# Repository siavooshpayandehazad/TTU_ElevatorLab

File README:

=================================================================
#   ____  ____  _  _                                            #     
#  (_  _)(_  _)/ )( \                                           #
#    )(    )(  ) \/ (                                           #
#   (__)  (__) \____/                                           #
#   ____  ____  _  _   __  ____  ____                           #
#  (  _ \(  __)( \/ ) /  \(_  _)(  __)                          #
#   )   / ) _) / \/ \(  O ) )(   ) _)                           #
#  (__\_)(____)\_)(_/ \__/ (__) (____)                          #
#   ____  __    ____  _  _   __  ____  __  ____                 #
#  (  __)(  )  (  __)/ )( \ / _\(_  _)/  \(  _ \                #
#   ) _) / (_/\ ) _) \ \/ //    \ )( (  O ))   /                #
#  (____)\____/(____) \__/ \_/\_/(__) \__/(__\_)                #
#   __     __   ____   __  ____   __  ____  __  ____  _  _      #
#  (  )   / _\ (  _ \ /  \(  _ \ / _\(_  _)/  \(  _ \( \/ )     #
#  / (_/\/    \ ) _ ((  O ))   //    \ )( (  O ))   / )  /      #
#  \____/\_/\_/(____/ \__/(__\_)\_/\_/(__) \__/(__\_)(__/       #
=================================================================
CONTRIBUTORS: 				SUPERVISOR:	
	SIAVOOSH PAYANDEH AZAD			PEETER ELLERVEEE
        HANNES KINKS
        MUHAMMAD ADEEL TAJAMMUL
	MAREK GRENCSTEIN
	RALF ANARI
INSITUTE:       TALLINN UNIVERSITY OF TECHNOLOGY 
                COMPUTER ENGINEERING DEPARTMENT        
YEAR:           2014
---------------------------
WIKI:           http://ati.ttu.ee/wiki/index.php/LIFT
DEMO:           https://www.youtube.com/watch?v=4VPq74wMY-0
---------------------------
NOTE: 		THE UPDATES IN SUB-PROJECTS ARE AVAILABLE IN BRANCHES. WE WILL 
		MERGE FOR EACH RELEASE.

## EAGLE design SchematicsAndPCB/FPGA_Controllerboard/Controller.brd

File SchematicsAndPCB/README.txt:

AUTHOR: SIAVOOSH PAYANDEH AZAD
YEAR:   2015

TODO: - DOUBLE CHECK WITH UCF FILE
      - MAKING A MICRO CONTROLLER BASED PCB

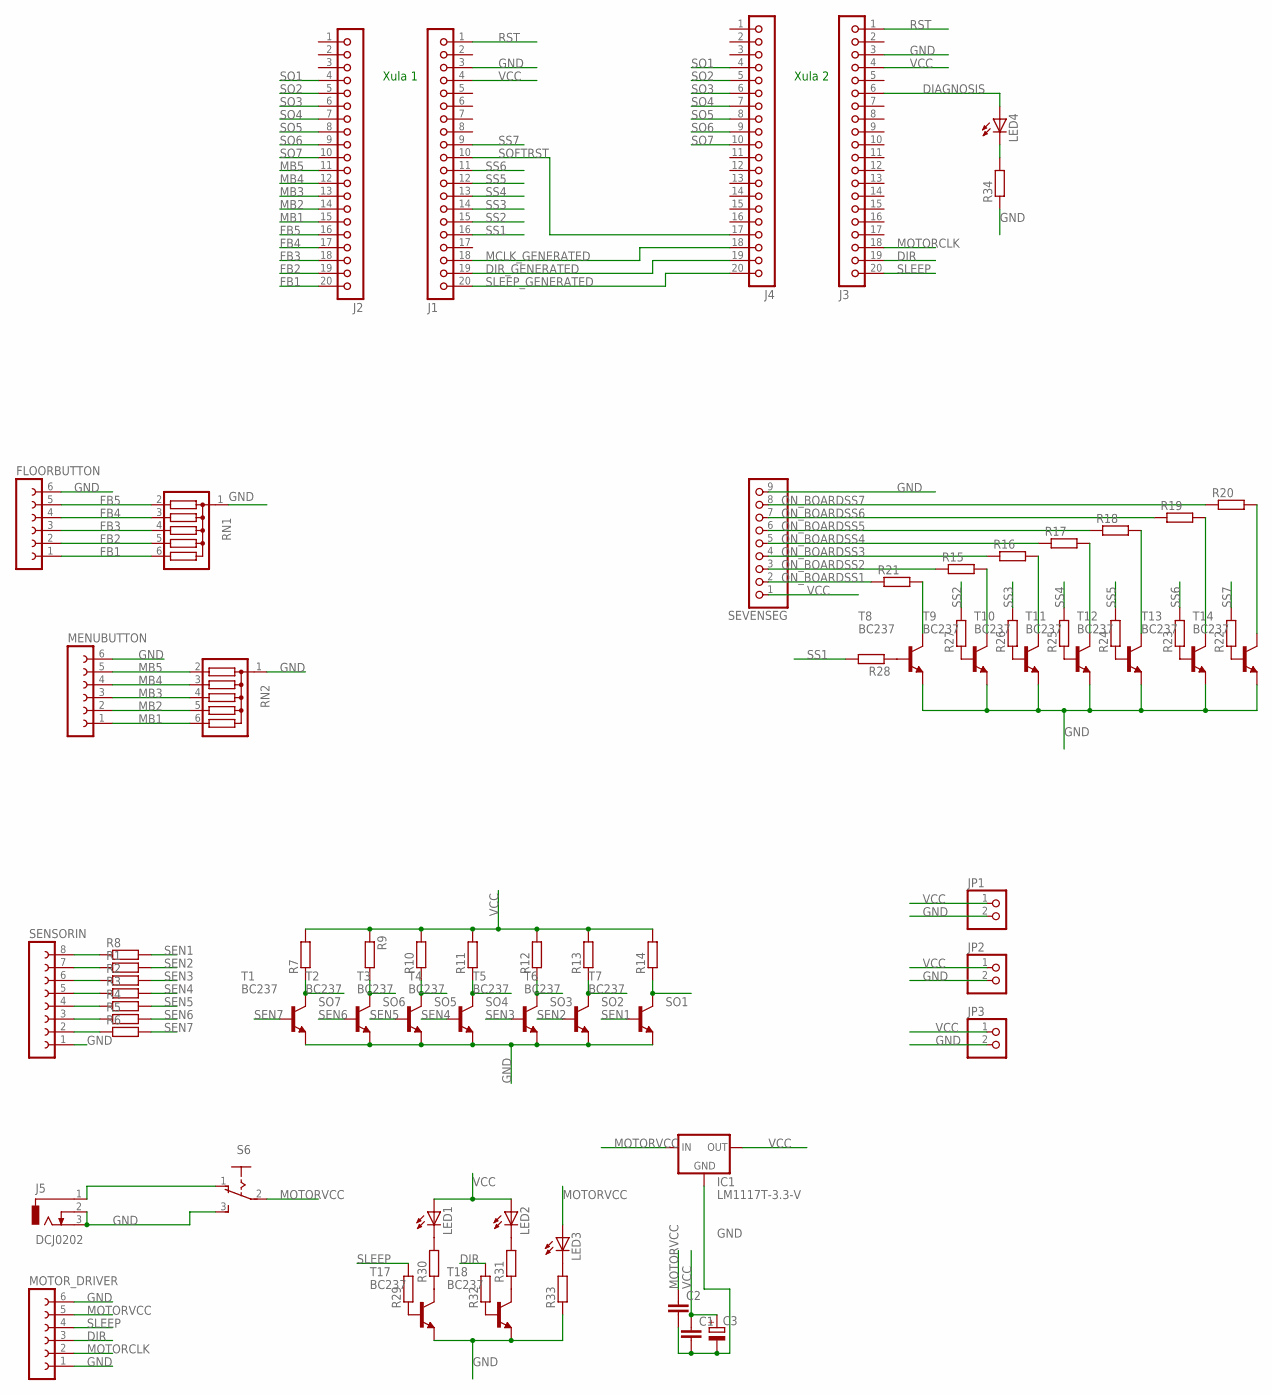
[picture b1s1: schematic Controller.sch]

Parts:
C1, C2: C-EU025-025X050; C025-025X050
C3: CPOL-EUE3.5-8; E3,5-8
FLOORBUTTON: FE06-1; FE06
IC1: LM1117T-3.3-V; TO220V
J1, J2, J3, J4: JBK20
J5: DCJ0202
JP1, JP2, JP3: PINHD-1X2; 1X02
LED1, LED2, LED3, LED4: LED3MM
MENUBUTTON: FE06-1; FE06
MOTOR_DRIVER: FE06-1; FE06
R1, R2, R3, R4, R5, R6, R7, R8, R9, R10, R11, R12, R13, R14, R15, R16, R17, R18, R19, R20, R21, R22, R23, R24, R25, R26, R27, R28, R29, R30, R31, R32, R33, R34: R-EU_0204/5; 0204/5
RN1, RN2: G05R; SIL6
S6: 255SB
SENSORIN: FE08-1; FE08
SEVENSEG: PINHD-1X9; 1X09-BIG
T1, T2, T3, T4, T5, T6, T7, T8, T9, T10, T11, T12, T13, T14, T17, T18: BC237; TO92

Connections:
DIAGNOSIS: J3.6, LED4.A
DIR: J3.19, MOTOR_DRIVER.3, R32.2
DIR_GENERATED: J1.19, J4.19
FB1: FLOORBUTTON.1, J2.20, RN1.6
FB2: FLOORBUTTON.2, J2.19, RN1.5
FB3: FLOORBUTTON.3, J2.18, RN1.4
FB4: FLOORBUTTON.4, J2.17, RN1.3
FB5: FLOORBUTTON.5, J2.16, RN1.2
GND: C1.2, C2.2, C3.-, FLOORBUTTON.6, IC1.1 (GND), J1.3, J3.3, J5.2, J5.3, JP1.2, JP2.2, JP3.2, MENUBUTTON.6, MOTOR_DRIVER.1, MOTOR_DRIVER.6, R33.1, R34.1, RN1.1, RN2.1, S6.3 (S), SENSORIN.1, SEVENSEG.9, T1.1 (E), T2.1 (E), T3.1 (E), T4.1 (E), T5.1 (E), T6.1 (E), T7.1 (E), T8.1 (E), T9.1 (E), T10.1 (E), T11.1 (E), T12.1 (E), T13.1 (E), T14.1 (E), T17.1 (E), T18.1 (E)
MB1: J2.15, MENUBUTTON.1, RN2.6
MB2: J2.14, MENUBUTTON.2, RN2.5
MB3: J2.13, MENUBUTTON.3, RN2.4
MB4: J2.12, MENUBUTTON.4, RN2.3
MB5: J2.11, MENUBUTTON.5, RN2.2
MCLK_GENERATED: J1.18, J4.18
MOTORCLK: J3.18, MOTOR_DRIVER.2
MOTORVCC: C2.1, IC1.3 (IN), LED3.A, MOTOR_DRIVER.5, S6.2
unnamed: R2.1, SENSORIN.6
unnamed: R21.2, T8.3 (C)
unnamed: LED4.K (C), R34.2
unnamed: R15.2, T9.3 (C)
unnamed: R16.2, T10.3 (C)
unnamed: R17.2, T11.3 (C)
unnamed: R18.2, T12.3 (C)
unnamed: R19.2, T13.3 (C)
unnamed: R5.1, SENSORIN.3
unnamed: R4.1, SENSORIN.4
unnamed: R3.1, SENSORIN.5
unnamed: R1.1, SENSORIN.7
unnamed: R8.1, SENSORIN.8
unnamed: R20.2, T14.3 (C)
unnamed: J5.1, S6.1 (O)
unnamed: R6.1, SENSORIN.2
unnamed: R22.1, T14.2 (B)
unnamed: R23.1, T13.2 (B)
unnamed: R24.1, T12.2 (B)
unnamed: R25.1, T11.2 (B)
unnamed: R26.1, T10.2 (B)
unnamed: R27.1, T9.2 (B)
unnamed: R28.1, T8.2 (B)
unnamed: R29.1, T17.2 (B)
unnamed: R30.1, T17.3 (C)
unnamed: R31.1, T18.3 (C)
unnamed: R32.1, T18.2 (B)
unnamed: LED3.K (C), R33.2
unnamed: LED1.K (C), R30.2
unnamed: LED2.K (C), R31.2
ON_BOARDSS1: R21.1, SEVENSEG.2
ON_BOARDSS2: R15.1, SEVENSEG.3
ON_BOARDSS3: R16.1, SEVENSEG.4
ON_BOARDSS4: R17.1, SEVENSEG.5
ON_BOARDSS5: R18.1, SEVENSEG.6
ON_BOARDSS6: R19.1, SEVENSEG.7
ON_BOARDSS7: R20.1, SEVENSEG.8
RST: J1.1, J3.1
SEN1: R8.2, T7.2 (B)
SEN2: R1.2, T6.2 (B)
SEN3: R2.2, T5.2 (B)
SEN4: R3.2, T4.2 (B)
SEN5: R4.2, T3.2 (B)
SEN6: R5.2, T2.2 (B)
SEN7: R6.2, T1.2 (B)
SLEEP: J3.20, MOTOR_DRIVER.4, R29.2
SLEEP_GENERATED: J1.20, J4.20
SO1: J2.4, J4.4, R14.1, T7.3 (C)
SO2: J2.5, J4.5, R13.1, T6.3 (C)
SO3: J2.6, J4.6, R12.1, T5.3 (C)
SO4: J2.7, J4.7, R11.1, T4.3 (C)
SO5: J2.8, J4.8, R10.1, T3.3 (C)
SO6: J2.9, J4.9, R9.2, T2.3 (C)
SO7: J2.10, J4.10, R7.1, T1.3 (C)
SOFTRST: J1.10, J4.17
SS1: J1.16, R28.2
SS2: J1.15, R27.2
SS3: J1.14, R26.2
SS4: J1.13, R25.2
SS5: J1.12, R24.2
SS6: J1.11, R23.2
SS7: J1.9, R22.2
VCC: C1.1, C3.+, IC1.2 (OUT), J1.4, J3.4, JP1.1, JP2.1, JP3.1, LED1.A, LED2.A, R7.2, R9.1, R10.2, R11.2, R12.2, R13.2, R14.2, SEVENSEG.1

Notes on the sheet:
Xula 1
Xula 2

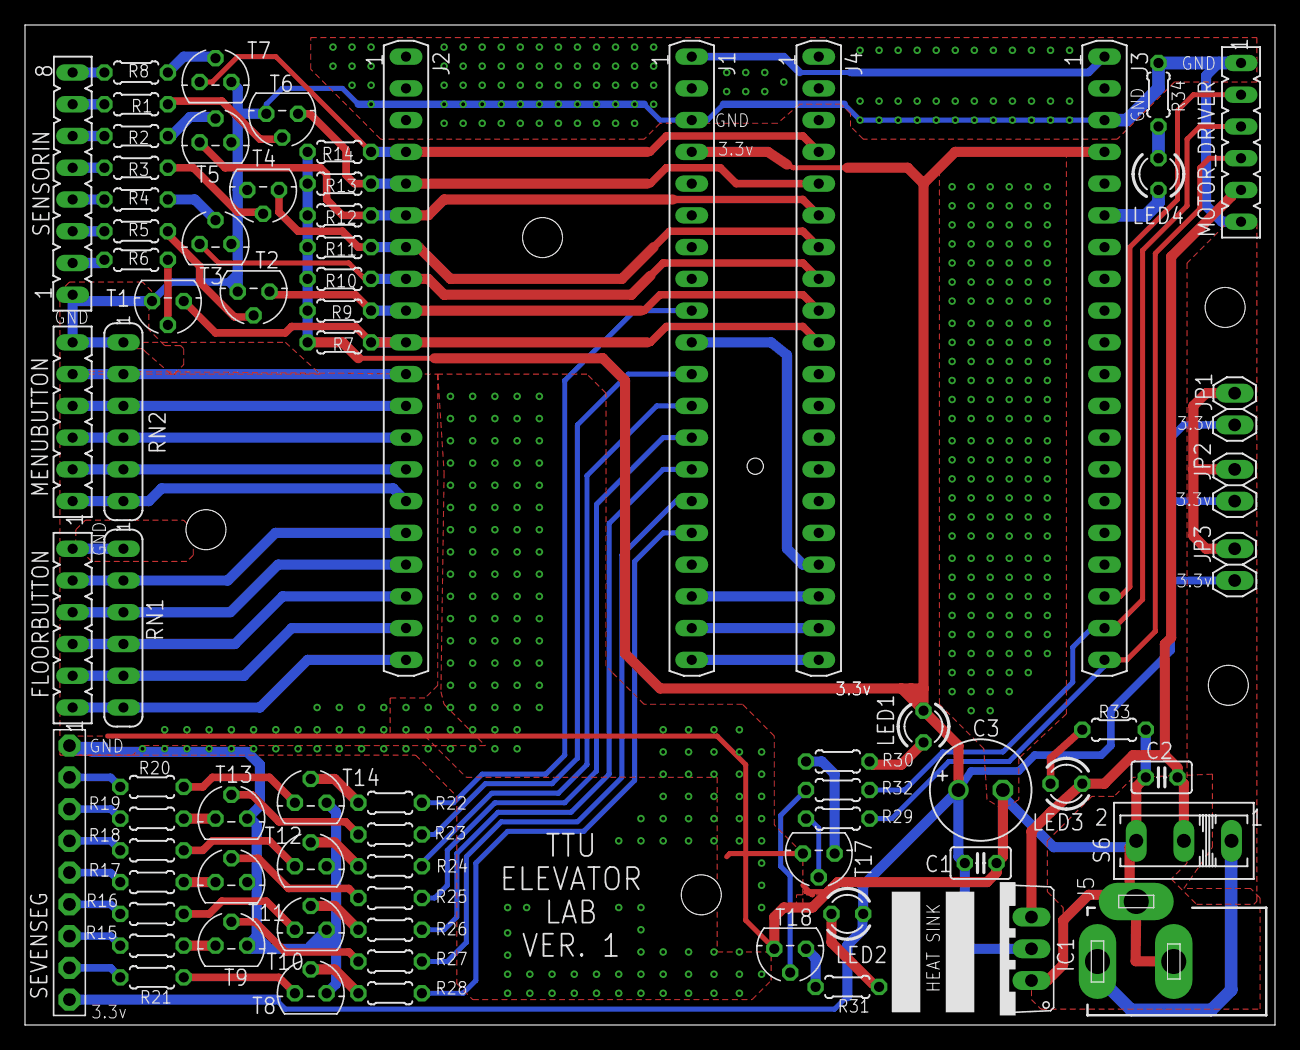
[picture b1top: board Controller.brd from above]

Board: 2 copper layers, 100.0 x 80.0 mm, 74 parts (0 on the bottom side), 80 nets.

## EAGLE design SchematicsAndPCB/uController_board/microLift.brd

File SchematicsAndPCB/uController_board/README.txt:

AUTHOR: SIAVOOSH PAYANDEH AZAD
YEAR:   2015

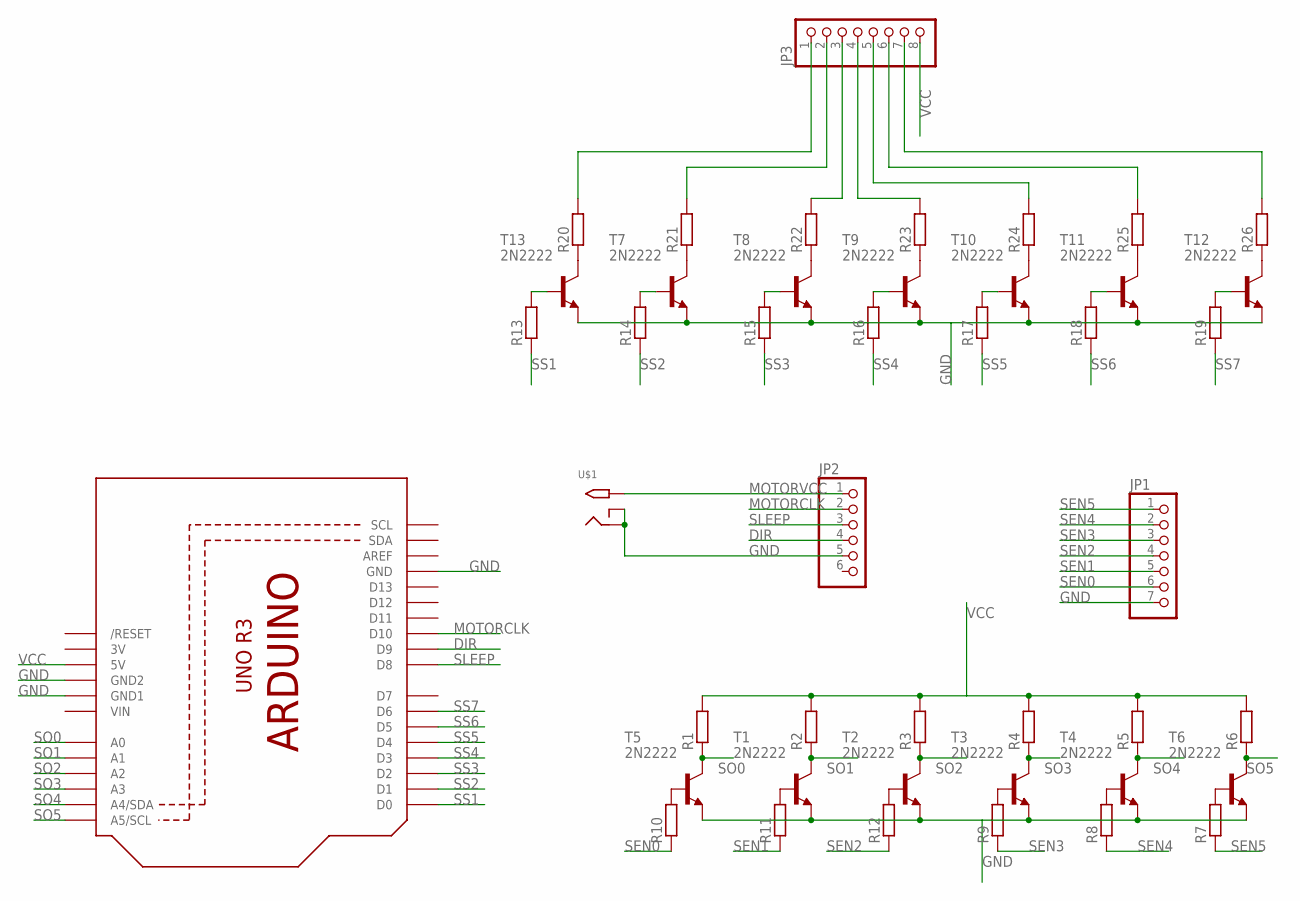
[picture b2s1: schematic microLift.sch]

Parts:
JP1: PINHD-1X7; 1X07
JP2: PINHD-1X6; 1X06
JP3: PINHD-1X8BIG; 1X08-BIG
Q1: ARDUINOR3-NOIOREF-NOTEXT; ARDUINOR3-NOTEXT-NOIOREF
R1, R2, R3, R4, R5, R6, R7, R8, R9, R10, R11, R12, R13, R14, R15, R16, R17, R18, R19, R20, R21, R22, R23, R24, R25, R26: R-EU_0204/7; 0204/7
T1, T2, T3, T4, T5, T6, T7, T8, T9, T10, T11, T12, T13: 2N2222; TO92-EBC-OVAL
U$1: 2.1MMJACKTHM; PJ-102A

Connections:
3V: Q1.3V
DIR: JP2.4, Q1.D9
GND: JP1.7, JP2.5, Q1.GND, Q1.GND1, Q1.GND2, T1.E, T2.E, T3.E, T4.E, T5.E, T6.E, T7.E, T8.E, T9.E, T10.E, T11.E, T12.E, T13.E, U$1.RING, U$1.RING_SW
MOTORCLK: JP2.2, Q1.D10
MOTORVCC: JP2.1, U$1.TIP
unnamed: R7.2, T6.B
unnamed: R8.2, T4.B
unnamed: R9.2, T3.B
unnamed: R10.2, T5.B
unnamed: R11.2, T1.B
unnamed: R12.2, T2.B
unnamed: R13.2, T13.B
unnamed: R14.2, T7.B
unnamed: R15.2, T8.B
unnamed: R16.2, T9.B
unnamed: R17.2, T10.B
unnamed: R18.2, T11.B
unnamed: R19.2, T12.B
unnamed: R20.1, T13.C
unnamed: R22.1, T8.C
unnamed: R23.1, T9.C
unnamed: R25.1, T11.C
unnamed: R26.1, T12.C
unnamed: R21.1, T7.C
unnamed: R24.1, T10.C
unnamed: JP3.4, R23.2
unnamed: JP3.3, R22.2
unnamed: JP3.2, R21.2
unnamed: JP3.1, R20.2
unnamed: JP3.5, R24.2
unnamed: JP3.6, R25.2
unnamed: JP3.7, R26.2
SEN0: JP1.6, R10.1
SEN1: JP1.5, R11.1
SEN2: JP1.4, R12.1
SEN3: JP1.3, R9.1
SEN4: JP1.2, R8.1
SEN5: JP1.1, R7.1
SLEEP: JP2.3, Q1.D8
SO0: Q1.A0, R1.1, T5.C
SO1: Q1.A1, R2.1, T1.C
SO2: Q1.A2, R3.1, T2.C
SO3: Q1.A3, R4.1, T3.C
SO4: Q1.A4 (A4/SDA), R5.1, T4.C
SO5: Q1.A5 (A5/SCL), R6.1, T6.C
SS1: Q1.D0, R13.1
SS2: Q1.D1, R14.1
SS3: Q1.D2, R15.1
SS4: Q1.D3, R16.1
SS5: Q1.D4, R17.1
SS6: Q1.D5, R18.1
SS7: Q1.D6, R19.1
VCC: JP3.8, Q1.5V, R1.2, R2.2, R3.2, R4.2, R5.2, R6.2
VIN: Q1.VIN

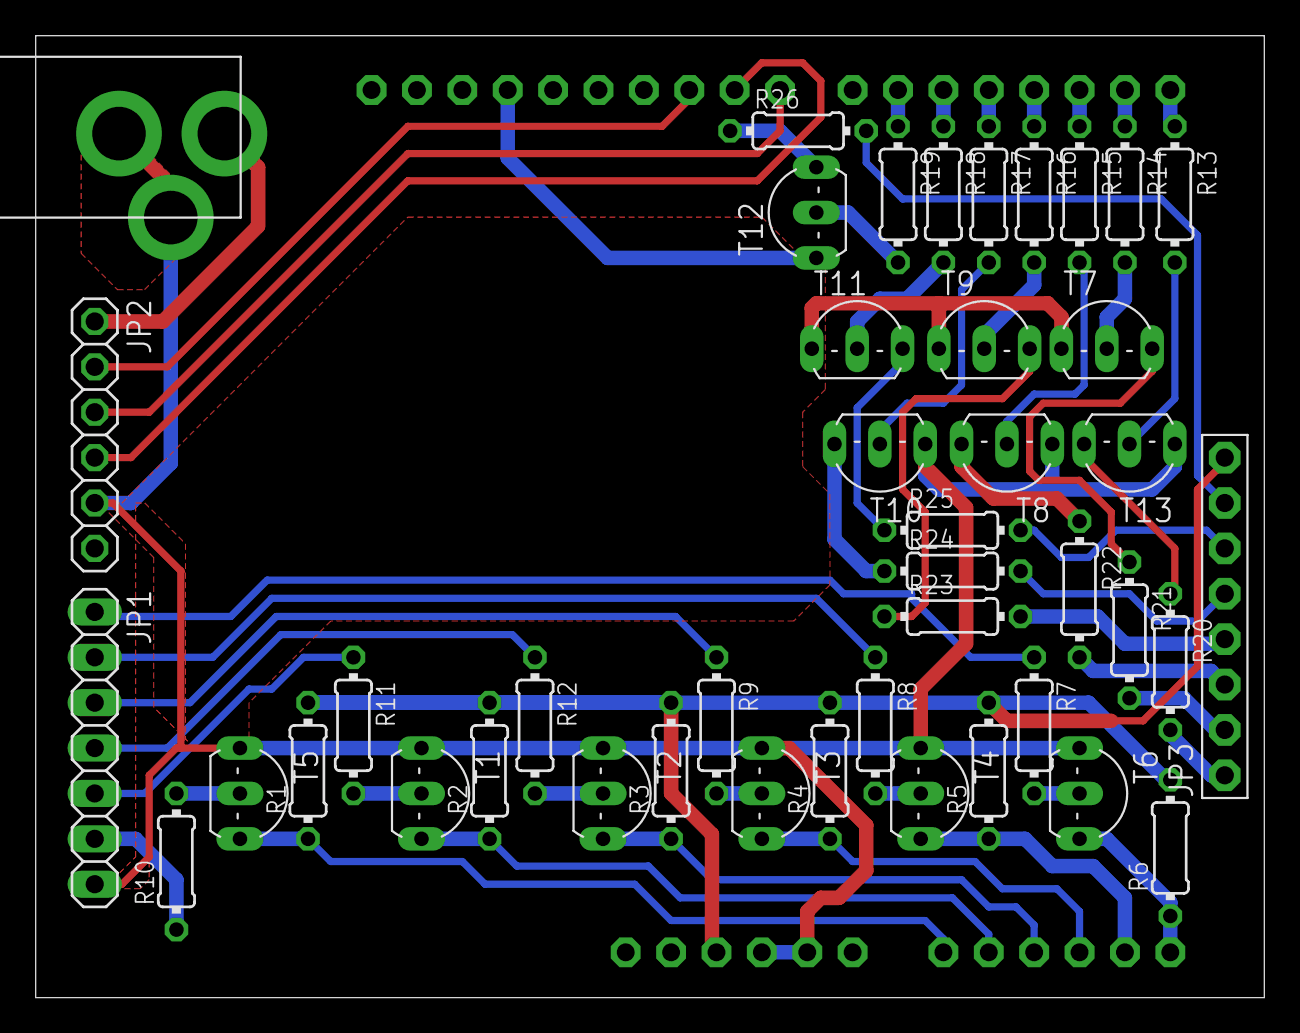
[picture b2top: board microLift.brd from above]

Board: 2 copper layers, 68.8 x 53.8 mm, 44 parts (0 on the bottom side), 52 nets.

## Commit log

2015-05-12 Commiting current web directory
2015-05-12 putting files in different folders
2015-05-12 Making different Folders
2015-05-12 added schematic file
2015-05-12 Some of the VHDL files
2015-05-13 re-naming
2015-05-15 Wrapper vhdl File Added
2015-05-15 Revert "Merge remote-tracking branch 'origin/master'"
    This reverts commit b9a0bb35ec9fad55c554c4c6ff2f16556dabe822, reversing
    changes made to 45b38cfc01e2318ebcf7d38d753fd94ed450e442.
2015-05-15 PCB in progress
2015-05-17 PCB Draft 1
    fully routed
2015-05-17 PCB Ver. 1
2015-05-17 Folder
2015-05-17 readme
2015-05-18 u-controller board draft
2015-05-19 3D MODEL
2015-05-19 update on u-controller board
2015-05-19 update on PCB
2015-05-19 re-commit
2015-05-19 FPGA PCB update
2015-05-20 additional vcc/gnd + holes + heatsink
2015-05-29 Update README.txt
    testchange
2015-05-29 getting ready for printing
2015-05-30 fixed typo
2015-11-18 Changed to web interface to TTU theme. Created index.php that takes into account request host when asking for camera feed.
2015-11-18 Removed old index files
